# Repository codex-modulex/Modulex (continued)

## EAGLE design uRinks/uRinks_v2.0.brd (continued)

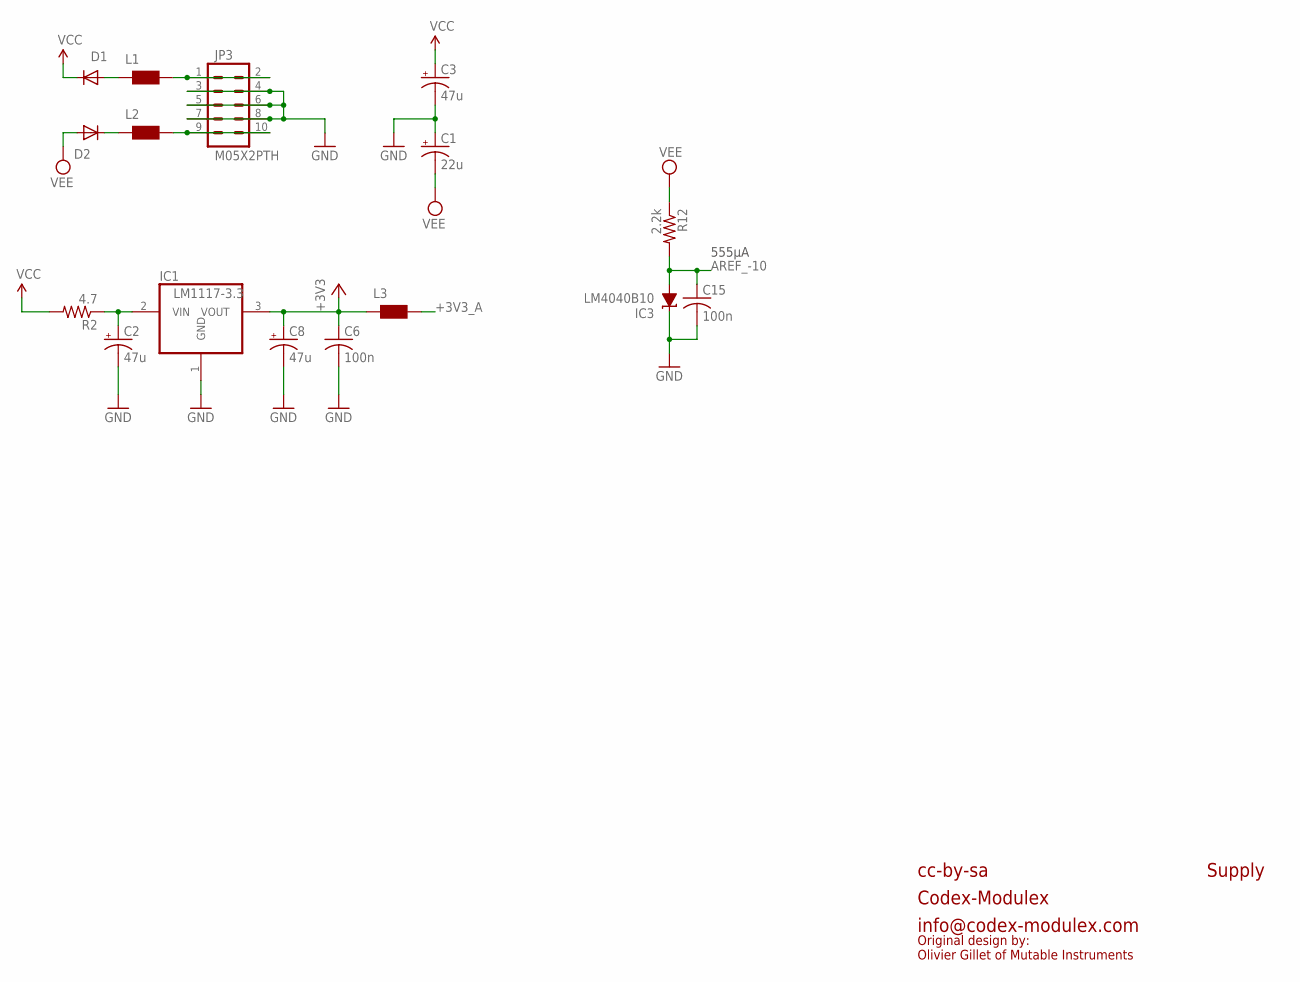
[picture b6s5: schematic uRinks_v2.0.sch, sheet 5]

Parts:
C1: 22u; PANASONIC_C
C2, C3, C8: 47u; PANASONIC_D
C6, C15: 100n; C0603
D1, D2: 1N5819HW; SOD123
IC1: LM1117-3.3; TO252
IC3: LM4040B10; DBZ_R-PDSO-G3
JP3: M05X2PTH; AVR_ICSP
L1, L2, L3: WE-CBF_0603; 0603
R2: 4.7; R1206
R12: 2.2k; R0603

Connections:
+3V3: C6.1, C8.+, IC1.3 (VOUT), L3.1; also elsewhere on the board
+3V3_A: L3.2; also elsewhere on the board
AREF_-10: C15.1, IC3.2 (A), R12.2; also elsewhere on the board
GND: C1.+, C2.-, C3.-, C6.2, C8.-, C15.2, IC1.1 (GND), IC3.1 (C), JP3.3, JP3.4, JP3.5, JP3.6, JP3.7, JP3.8; also elsewhere on the board
unnamed: C2.+, IC1.2 (VIN), R2.1
unnamed: D1.A, L1.1
unnamed: D2.C, L2.1
unnamed: JP3.1, JP3.2, L1.2
unnamed: JP3.9, JP3.10, L2.2
VCC: C3.+, D1.C, R2.2; also elsewhere on the board
VEE: C1.-, D2.A, R12.1; also elsewhere on the board

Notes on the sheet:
555µA
cc-by-sa
Codex-Modulex
info@codex-modulex.com
Supply
Original design by: Olivier Gillet of Mutable Instruments

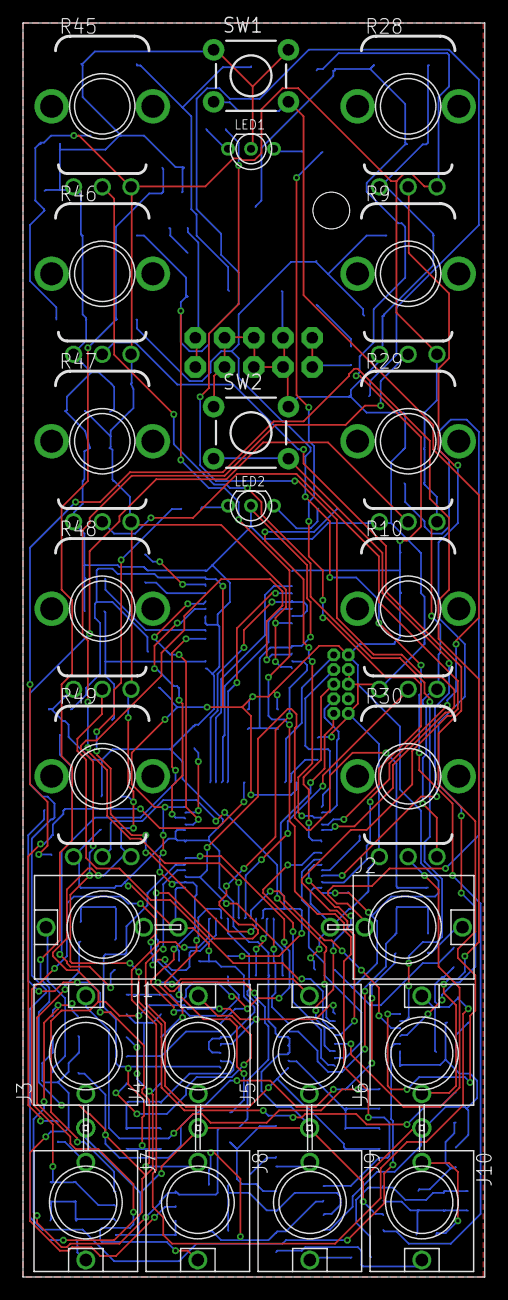
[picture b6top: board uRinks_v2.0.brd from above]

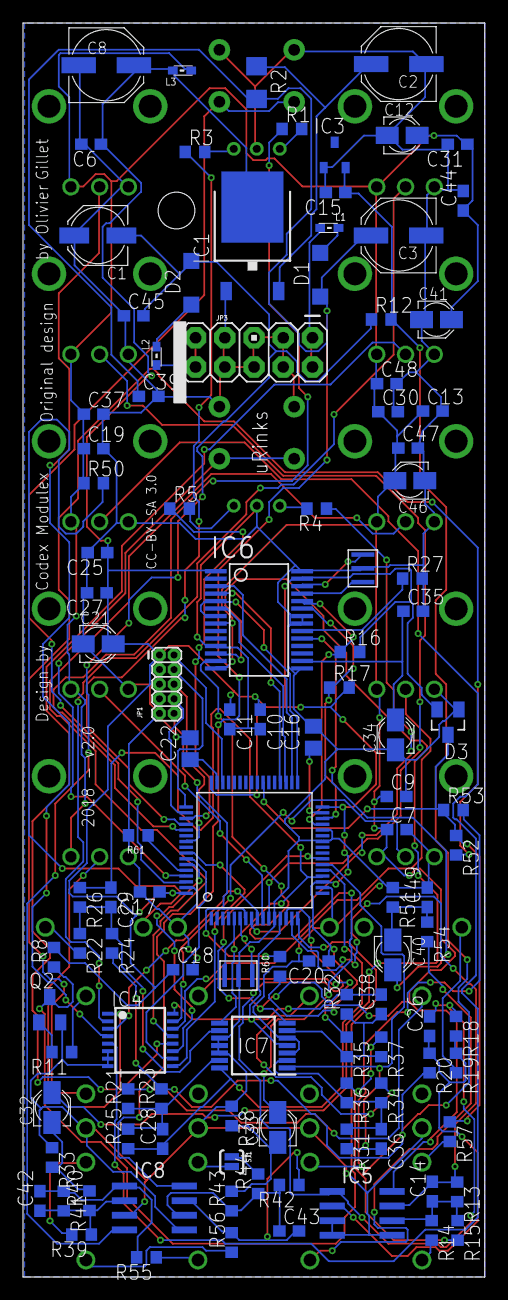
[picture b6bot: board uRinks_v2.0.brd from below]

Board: 2 copper layers, 40.1 x 109.0 mm, 136 parts (112 on the bottom side), 97 nets.

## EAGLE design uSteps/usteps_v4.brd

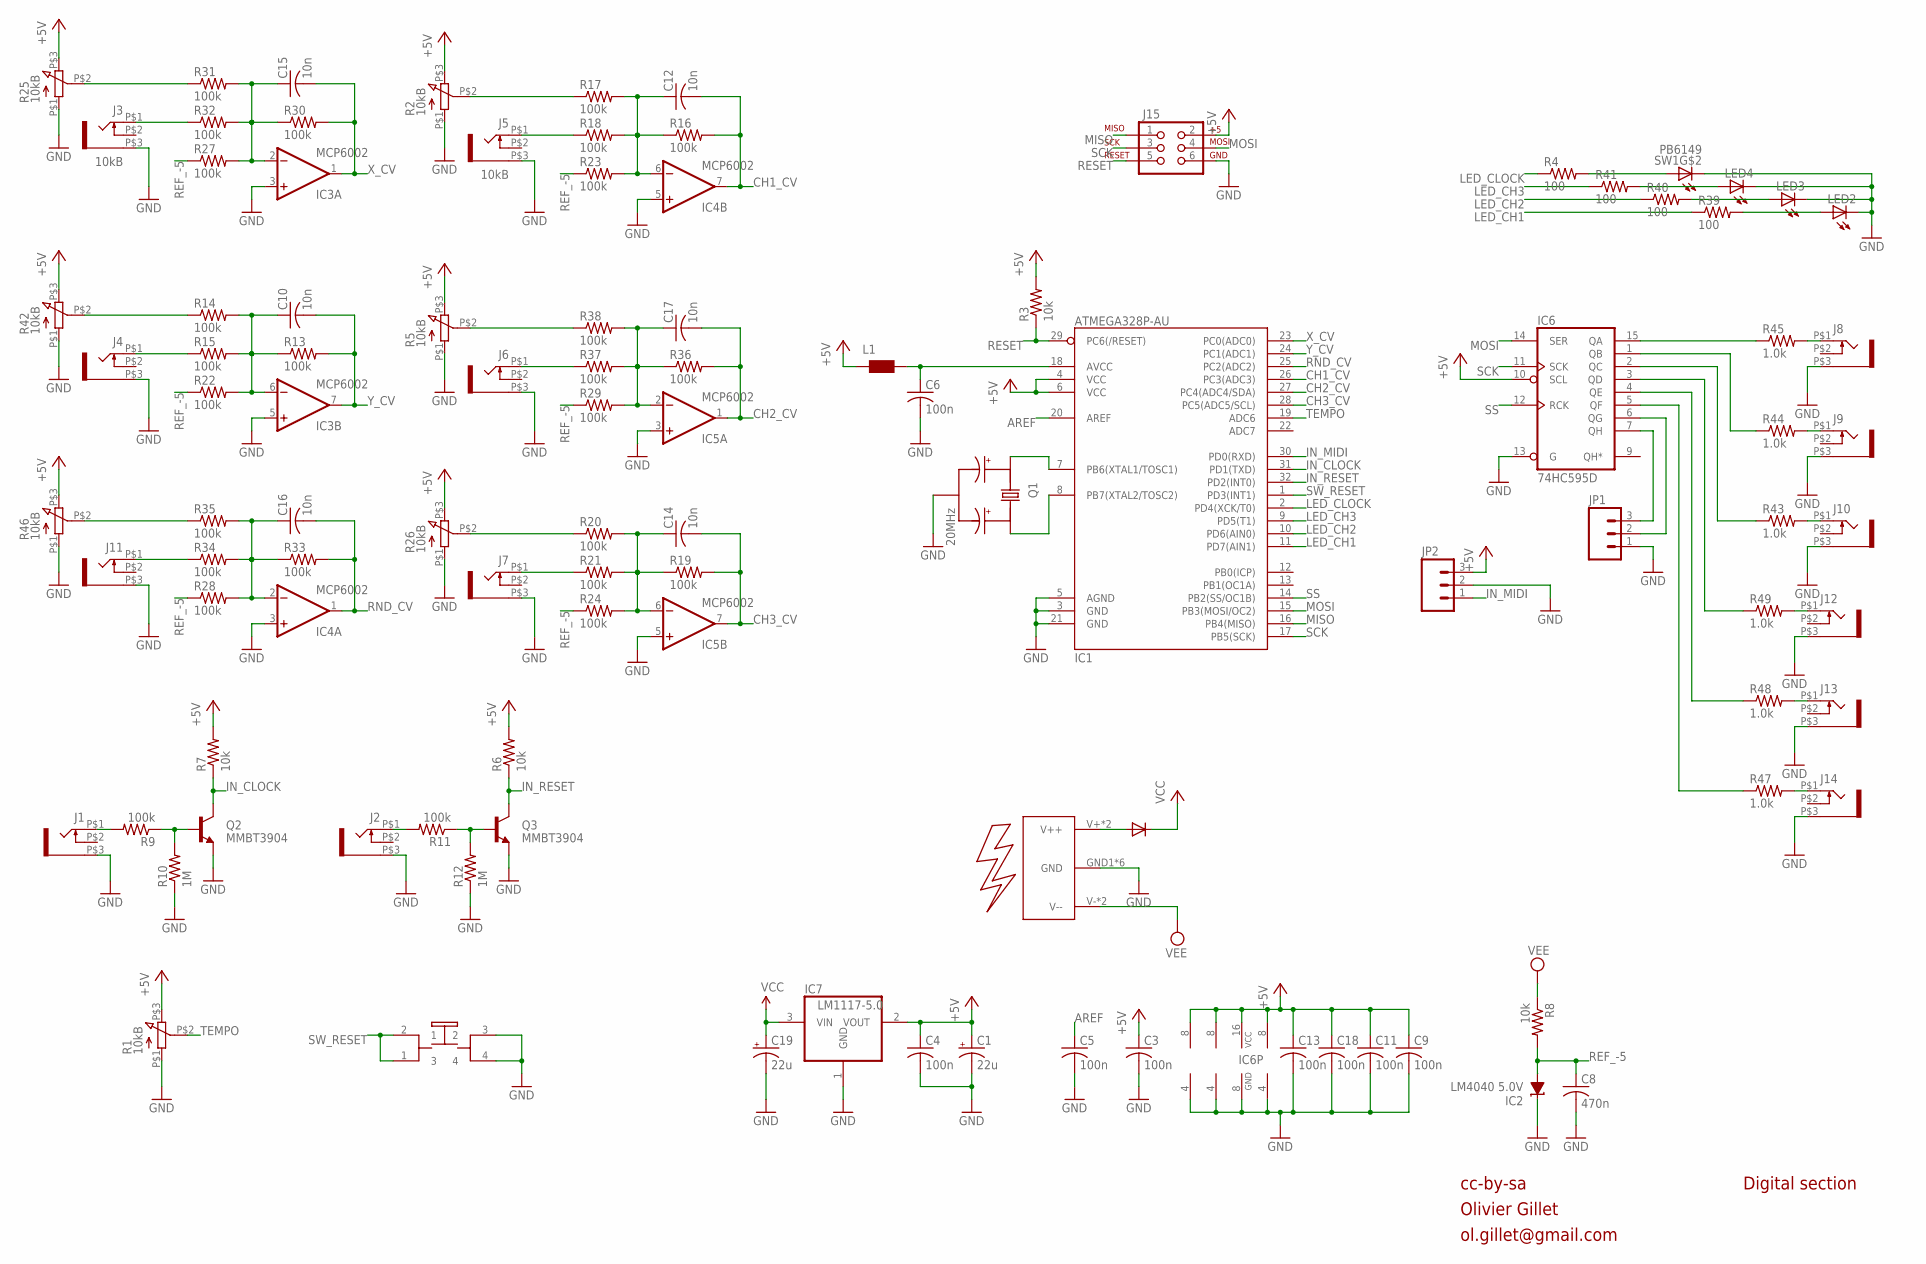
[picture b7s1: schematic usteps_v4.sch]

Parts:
C1, C19: 22u; PANASONIC_C
C3, C4, C5, C6, C9, C11, C13, C18: 100n; C0603
C8: 470n; C0603
C10, C12, C14, C15, C16, C17: 10n; C0603
D2: 1N5819HW; SOD123
IC1: ATMEGA328P-AU; TQFP32-08
IC2: LM4040 5.0V; DBZ_R-PDSO-G3
IC3, IC4, IC5: MCP6002; SO08
IC6: 74HC595D; SO16
IC7: LM1117-5.0; SOT223
J1, J2, J4, J6, J7, J8, J9, J10, J11, J12, J13, J14: WQP-PJ301M-12_JACK
J3, J5: 10kB; WQP-PJ301M-12_JACK
J15: AVR_SPI_PRG_6PTH; 2X3
JP1, JP2: M03PTH; 1X03
L1: WE-CBF_0603; 0603
LED2, LED3, LED4: LED3MM
Q1: 20MHz; INSTRUO_CRYSTAL_SMALLER
Q2, Q3: MMBT3904; SOT23-BEC
R1, R2, R5, R25, R26, R42, R46: 10kB; INSTRUO_Q-POT2
R3, R6, R7, R8: 10k; R0603
R4, R39, R40, R41: 100; R0603
R9, R11, R13, R14, R15, R16, R17, R18, R19, R20, R21, R22, R23, R24, R27, R28, R29, R30, R31, R32, R33, R34, R35, R36, R37, R38: 100k; R0603
R10, R12: 1M; R0603
R43, R44, R45, R47, R48, R49: 1.0k; R0603
SW1: PB6149; INSTRUO_PB6149L
U$1: INSTRUO_EURO_POWER2

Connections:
+5V: C1.+, C3.1, C4.1, C9.1, C11.1, C13.1, C18.1, IC1.4 (VCC), IC1.6 (VCC), IC3.8 (V+), IC4.8 (V+), IC5.8 (V+), IC6.10 (SCL), IC6.16 (VCC), IC7.2 (VOUT), J15.2, JP2.3, L1.1, R1.P$3 (3), R2.P$3 (3), R3.2, R5.P$3 (3), R6.2, R7.2, R25.P$3 (3), R26.P$3 (3), R42.P$3 (3), R46.P$3 (3)
AREF: C5.1, IC1.20 (AREF)
CH1_CV: C12.2, IC1.26 (PC3(ADC3)), IC4.7 (OUT), R16.2
CH2_CV: C17.2, IC1.27 (PC4(ADC4/SDA)), IC5.1 (OUT), R36.2
CH3_CV: C14.2, IC1.28 (PC5(ADC5/SCL)), IC5.7 (OUT), R19.2
CLOCK_OUT: IC6.6 (QG), JP1.2
GATE1_IN: J1.P$1 (2), R9.2
GATE1_LED: R4.2, SW1.A
GATE2_IN: J2.P$1 (2), R11.2
GATE2_LED: LED4.A, R41.2
GATE3_LED: LED3.A, R40.2
GATE4_LED: LED2.A, R39.2
GND: C1.-, C3.2, C4.2, C5.2, C6.2, C8.2, C9.2, C11.2, C13.2, C18.2, C19.-, IC1.3 (GND), IC1.5 (AGND), IC1.21 (GND), IC2.1 (C), IC3.3 (+IN), IC3.4 (V-), IC3.5 (+IN), IC4.3 (+IN), IC4.4 (V-), IC4.5 (+IN), IC5.3 (+IN), IC5.4 (V-), IC5.5 (+IN), IC6.8 (GND), IC6.13 (G), IC7.1 (GND), J1.P$3 (1), J2.P$3 (1), J3.P$3 (1), J4.P$3 (1), J5.P$3 (1), J6.P$3 (1), J7.P$3 (1), J8.P$3 (1), J9.P$3 (1), J10.P$3 (1), J11.P$3 (1), J12.P$3 (1), J13.P$3 (1), J14.P$3 (1), J15.6, JP1.1, JP2.2, LED2.K (C), LED3.K (C), LED4.K (C), Q1.GND, Q2.E, Q3.E, R1.P$1 (1), R2.P$1 (1), R5.P$1 (1), R10.1, R12.1, R25.P$1 (1), R26.P$1 (1), R42.P$1 (1), R46.P$1 (1), SW1.3 (2), SW1.4, SW1.K (C), U$1.GND1 (GND), U$1.GND2 (GND), U$1.GND3 (GND), U$1.GND4 (GND), U$1.GND5 (GND), U$1.GND6 (GND)
IN_CLOCK: IC1.31 (PD1(TXD)), Q2.C, R7.1
IN_MIDI: IC1.30 (PD0(RXD)), JP2.1
IN_RESET: IC1.32 (PD2(INT0)), Q3.C, R6.1
LED_CH1: IC1.11 (PD7(AIN1)), R39.1
LED_CH2: IC1.10 (PD6(AIN0)), R40.1
LED_CH3: IC1.9 (PD5(T1)), R41.1
LED_CLOCK: IC1.2 (PD4(XCK/T0)), R4.1
MISO: IC1.16 (PB4(MISO)), J15.1
MOSI: IC1.15 (PB3(MOSI/OC2)), IC6.14 (SER), J15.4
unnamed: Q2.B, R9.1, R10.2
unnamed: Q3.B, R11.1, R12.2
unnamed: IC1.7 (PB6(XTAL1/TOSC1)), Q1.X1
unnamed: J14.P$1 (2), R47.2
unnamed: J13.P$1 (2), R48.2
unnamed: J12.P$1 (2), R49.2
unnamed: IC1.8 (PB7(XTAL2/TOSC2)), Q1.X2
unnamed: D2.A, U$1.V+ (V++), U$1.V++
unnamed: R25.P$2 (2), R31.1
unnamed: J3.P$1 (2), R32.1
unnamed: C10.1, IC3.6 (-IN), R13.1, R14.2, R15.2, R22.2
unnamed: R14.1, R42.P$2 (2)
unnamed: J4.P$1 (2), R15.1
unnamed: C16.1, IC4.2 (-IN), R28.2, R33.1, R34.2, R35.2
unnamed: R35.1, R46.P$2 (2)
unnamed: J11.P$1 (2), R34.1
unnamed: C12.1, IC4.6 (-IN), R16.1, R17.2, R18.2, R23.2
unnamed: R2.P$2 (2), R17.1
unnamed: J5.P$1 (2), R18.1
unnamed: C17.1, IC5.2 (-IN), R29.2, R36.1, R37.2, R38.2
unnamed: R5.P$2 (2), R38.1
unnamed: J6.P$1 (2), R37.1
unnamed: C14.1, IC5.6 (-IN), R19.1, R20.2, R21.2, R24.2
unnamed: R20.1, R26.P$2 (2)
unnamed: J7.P$1 (2), R21.1
unnamed: IC6.15 (QA), R45.1
unnamed: IC6.1 (QB), R44.1
unnamed: C15.1, IC3.2 (-IN), R27.2, R30.1, R31.2, R32.2
unnamed: IC6.2 (QC), R43.1
unnamed: IC6.3 (QD), R49.1
unnamed: IC6.4 (QE), R48.1
unnamed: IC6.5 (QF), R47.1
unnamed: J8.P$1 (2), R45.2
unnamed: J9.P$1 (2), R44.2
unnamed: J10.P$1 (2), R43.2
unnamed: C6.1, IC1.18 (AVCC), L1.2
RANDOM_GATE: IC6.7 (QH), JP1.3
REF_-5: C8.1, IC2.2 (A), R8.2, R22.1, R23.1, R24.1, R27.1, R28.1, R29.1
RESET: IC1.29 (PC6(/RESET)), J15.5, R3.1
RND_CV: C16.2, IC1.25 (PC2(ADC2)), IC4.1 (OUT), R33.2
SCK: IC1.17 (PB5(SCK)), IC6.11 (SCK), J15.3
SS: IC1.14 (PB2(SS/OC1B)), IC6.12 (RCK)
SW_RESET: IC1.1 (PD3(INT1)), SW1.1 (3), SW1.2 (1)
TEMPO: IC1.19 (ADC6), R1.P$2 (2)
VCC: C19.+, D2.C, IC7.3 (VIN)
VEE: R8.1, U$1.V- (V--), U$1.V--
X_CV: C15.2, IC1.23 (PC0(ADC0)), IC3.1 (OUT), R30.2
Y_CV: C10.2, IC1.24 (PC1(ADC1)), IC3.7 (OUT), R13.2

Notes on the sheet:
cc-by-sa
Olivier Gillet
ol.gillet@gmail.com
Digital section

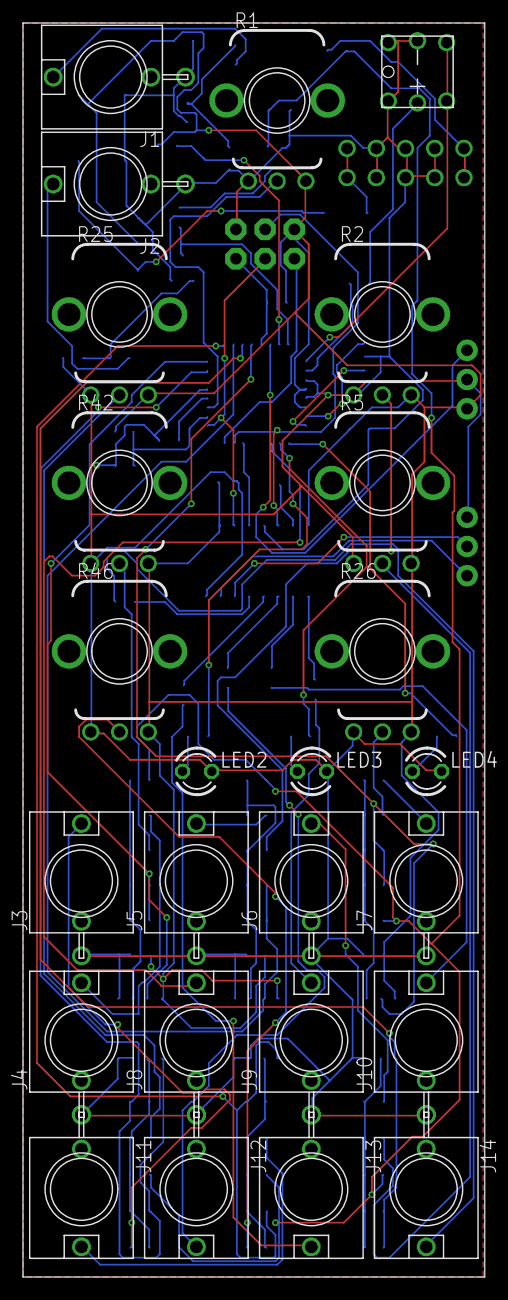
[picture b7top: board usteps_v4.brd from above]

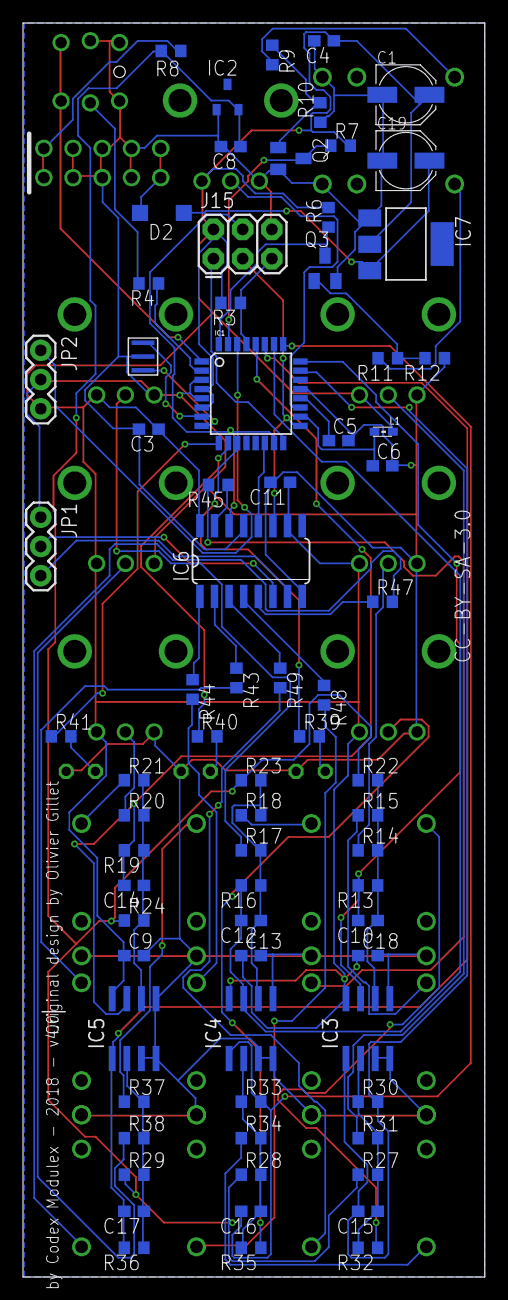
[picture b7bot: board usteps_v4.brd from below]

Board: 2 copper layers, 40.1 x 109.0 mm, 100 parts (75 on the bottom side), 70 nets.
